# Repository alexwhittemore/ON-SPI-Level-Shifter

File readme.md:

The ON SPI Level Shifter is very similar to the ON Level Shifter at https://github.com/alexwhittemore/ON-Level-Shifter. It employs the ON Semi MC74VHC1GT126 to shift voltage levels from 2.5V or 3.3V on the low side to 3.3V or 5V on the high side. Wire the master to the master side, the slave to the slave side, and attach their respective power supplies. Either master or slave may be the high side.

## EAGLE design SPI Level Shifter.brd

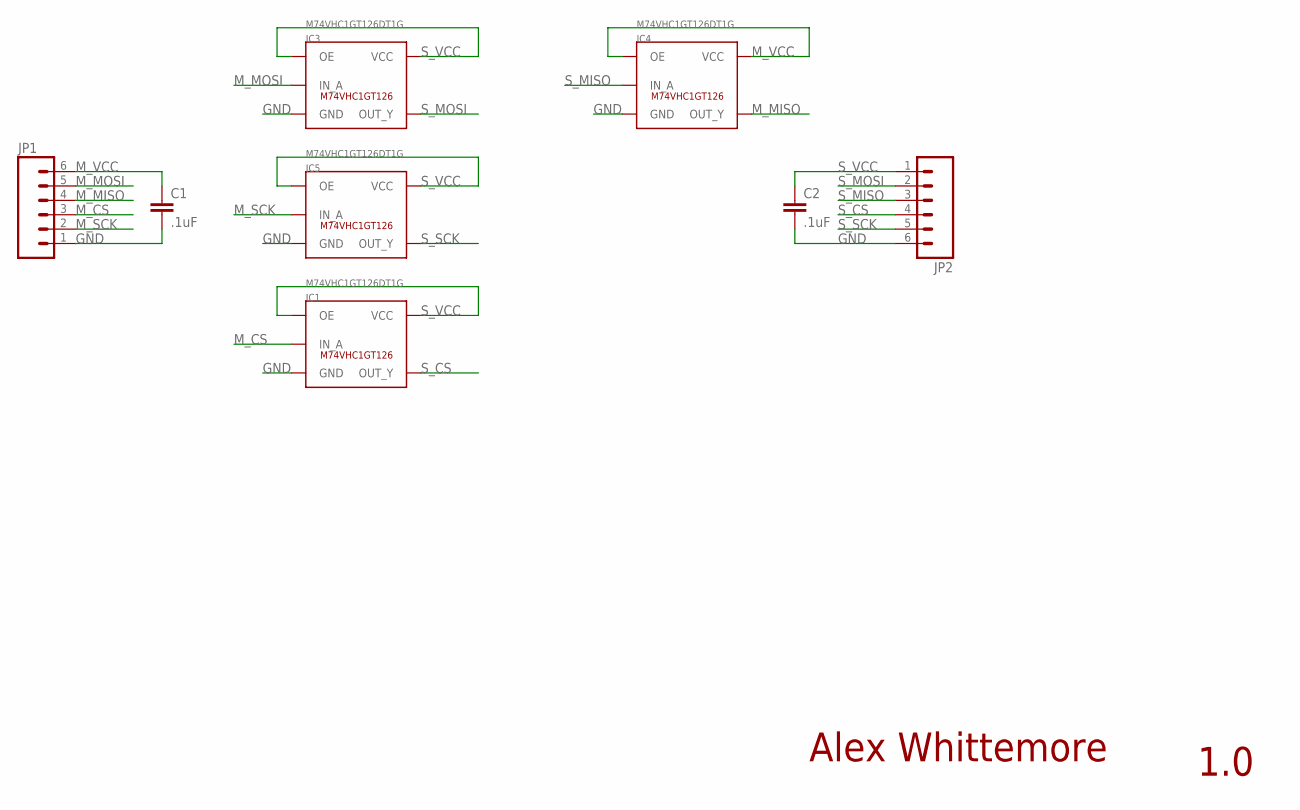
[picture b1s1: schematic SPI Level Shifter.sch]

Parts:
C1, C2: .1uF; 0402-CAP
IC1, IC3, IC4, IC5: M74VHC1GT126DT1G; SOT23-5L
JP1, JP2: M06LOCK; 1X06_LOCK

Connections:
GND: C1.2, C2.2, IC1.3 (GND), IC3.3 (GND), IC4.3 (GND), IC5.3 (GND), JP1.1, JP2.6
M_CS: IC1.2 (IN_A), JP1.3
M_MISO: IC4.4 (OUT_Y), JP1.4
M_MOSI: IC3.2 (IN_A), JP1.5
M_SCK: IC5.2 (IN_A), JP1.2
M_VCC: C1.1, IC4.1 (OE), IC4.5 (VCC), JP1.6
S_CS: IC1.4 (OUT_Y), JP2.4
S_MISO: IC4.2 (IN_A), JP2.3
S_MOSI: IC3.4 (OUT_Y), JP2.2
S_SCK: IC5.4 (OUT_Y), JP2.5
S_VCC: C2.1, IC1.1 (OE), IC1.5 (VCC), IC3.1 (OE), IC3.5 (VCC), IC5.1 (OE), IC5.5 (VCC), JP2.1

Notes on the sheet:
Alex Whittemore
1.0

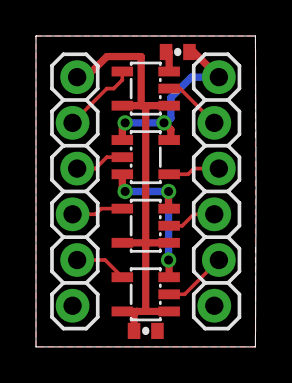
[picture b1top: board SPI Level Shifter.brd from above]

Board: 2 copper layers, 12.2 x 17.3 mm, 8 parts (0 on the bottom side), 11 nets.

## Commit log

2012-09-18 Initial commit. Added readme.
2012-09-18 Edited silkscreen layout to make things more straightforward and tidy.
2013-06-20 ignore eagle.epf

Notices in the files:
parts and their libraries:
SparkFun-Connectors: Licensing: CC v3.0 Share-Alike You are welcome to use this library for commercial purposes.
AlexW-Eagle-Libraries: Released under the Creative Commons
AlexW-Eagle-Libraries: http://creativecommons.org/licenses/by-sa/3.0
